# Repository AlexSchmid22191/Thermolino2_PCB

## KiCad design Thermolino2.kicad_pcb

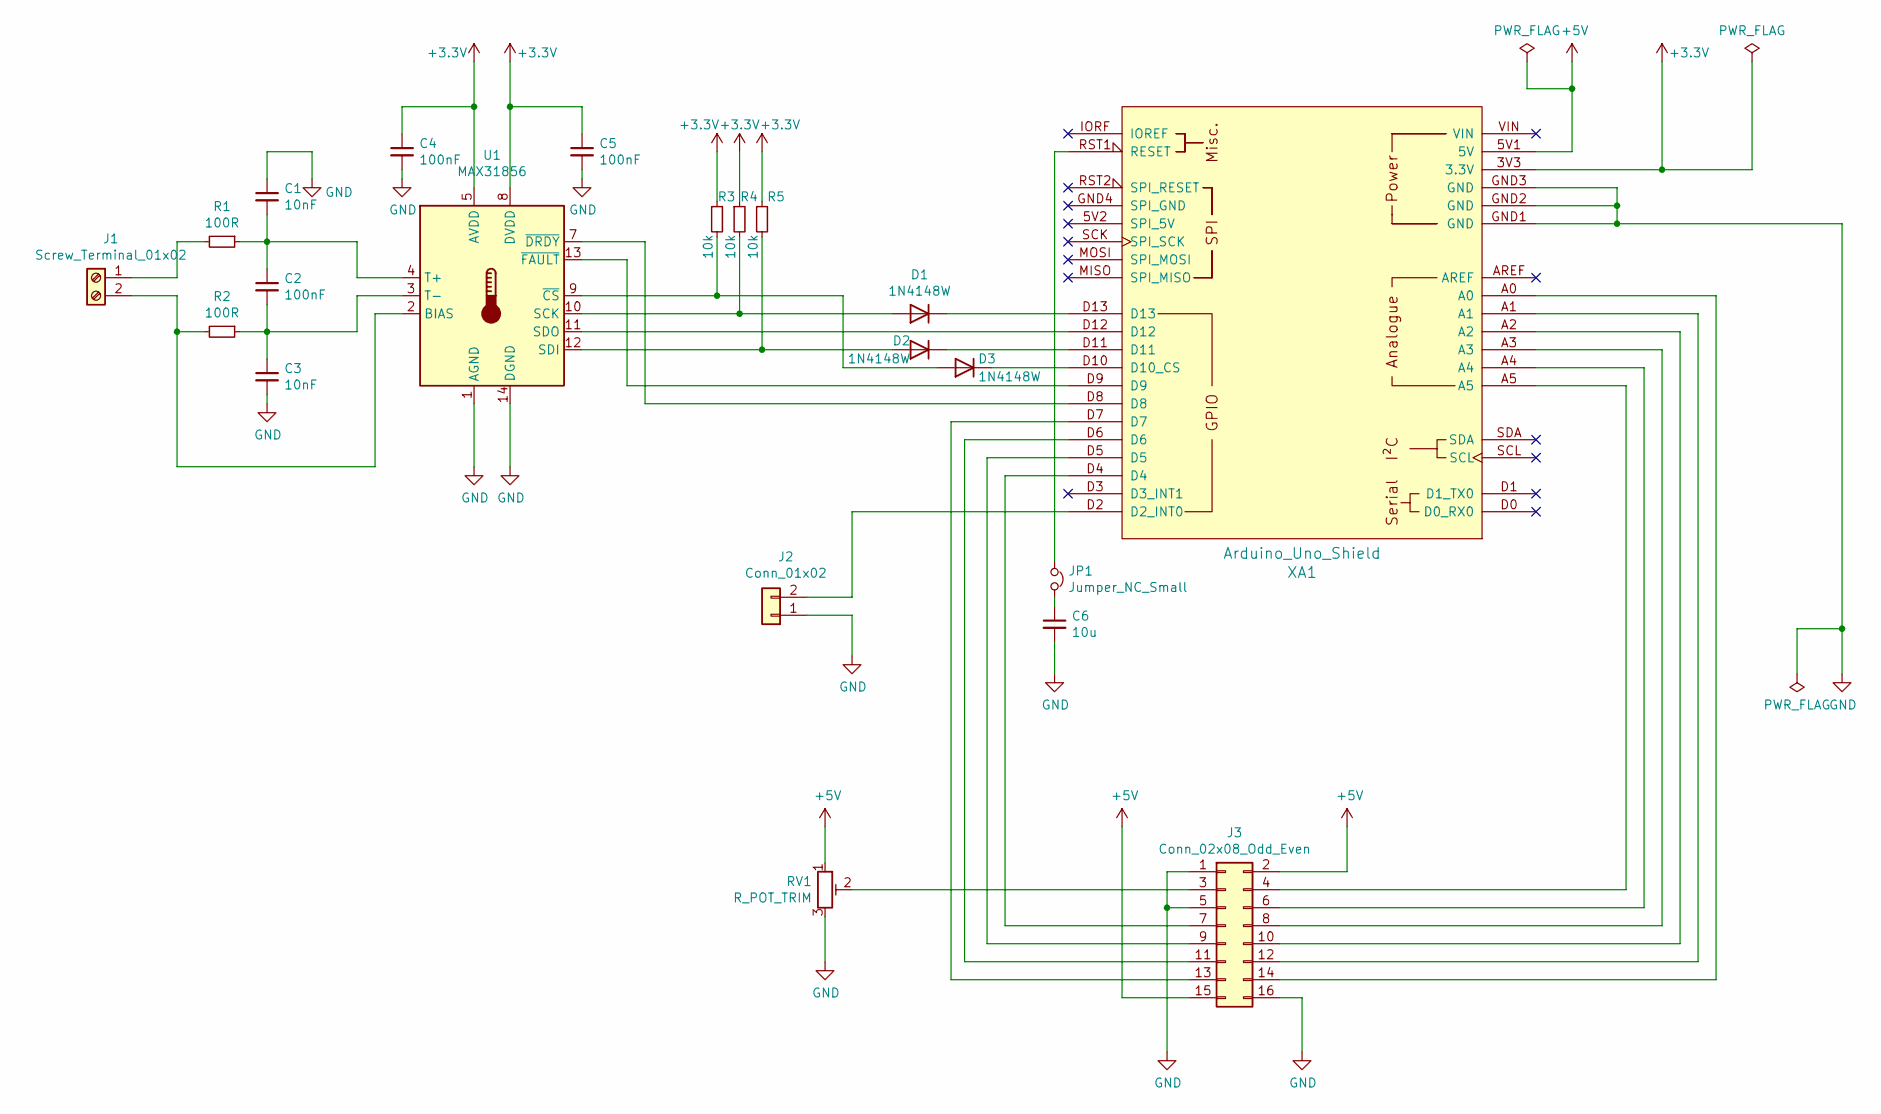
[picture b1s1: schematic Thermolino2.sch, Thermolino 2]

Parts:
C1, C3: 10nF; C_0603_1608Metric; LCSC C57112
C2, C4, C5: 100nF; C_0603_1608Metric; LCSC C14663
C6: 10u; C_0603_1608Metric_Pad1.05x0.95mm_HandSolder; LCSC C19702
D1, D2, D3: 1N4148W; D_SOD-123; LCSC C81598
J1: Screw_Terminal_01x02; Wurth_ScrewTerminal_02
J2: Conn_01x02; PinHeader_1x02_P2.54mm_Vertical
J3: Conn_02x08_Odd_Even; IDC_02x08
JP1: Jumper_NC_Small; PinHeader_1x02_P2.54mm_Vertical
R1, R2: 100R; R_0603_1608Metric; LCSC C22775
R3, R4, R5: 10k; R_0603_1608Metric; LCSC C25804
RV1: R_POT_TRIM; Vishay_TS53_Trimpot
U1: MAX31856; TSSOP-14_4.4x5mm_P0.65mm; LCSC C116632
XA1: Arduino_Uno_Shield

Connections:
+3V3: C4.1, C5.1, R3.1, R4.1, R5.1, U1.5 (AVDD), U1.8 (DVDD), XA1.3V3 (3.3V)
+5V: J3.2, J3.15, RV1.1, XA1.5V1 (5V)
GND: C1.1, C3.2, C4.2, C5.2, C6.2, J2.1, J3.1, J3.5, J3.16, RV1.3, U1.1 (AGND), U1.14 (DGND), XA1.GND1 (GND), XA1.GND2 (GND), XA1.GND3 (GND)
unnamed: C1.2, C2.1, R1.1, U1.4 (T+)
unnamed: C2.2, C3.1, R2.1, U1.3 (T-)
unnamed: C6.1, JP1.2
unnamed: D1.1 (K), XA1.D13
unnamed: D1.2 (A), R4.2, U1.10 (SCK)
unnamed: D2.1 (K), XA1.D11
unnamed: D2.2 (A), R5.2, U1.12 (SDI)
unnamed: D3.1 (K), XA1.D10 (D10_CS)
unnamed: D3.2 (A), R3.2, U1.9 (~CS)
unnamed: J1.1, R1.2
unnamed: J1.2, R2.2, U1.2 (BIAS)
unnamed: J2.2, XA1.D2 (D2_INT0)
unnamed: J3.3, RV1.2
unnamed: J3.4, XA1.A5
unnamed: J3.6, XA1.A4
unnamed: J3.7, XA1.D4
unnamed: J3.8, XA1.A3
unnamed: J3.9, XA1.D5
unnamed: J3.10, XA1.A2
unnamed: J3.11, XA1.D6
unnamed: J3.12, XA1.A1
unnamed: J3.13, XA1.D7
unnamed: J3.14, XA1.A0
unnamed: JP1.1, XA1.RST1 (RESET)
unnamed: U1.7 (~DRDY), XA1.D8
unnamed: U1.11 (SDO), XA1.D12
unnamed: U1.13 (~FAULT), XA1.D9

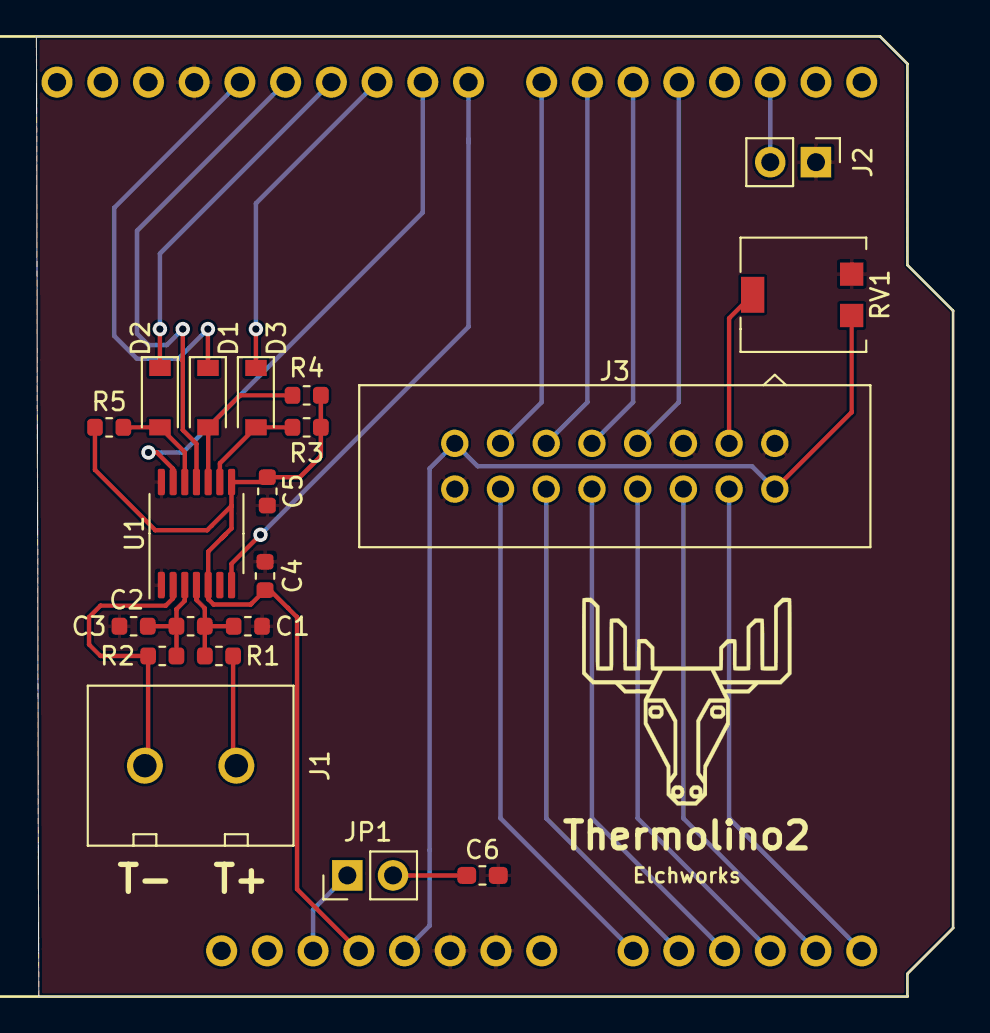
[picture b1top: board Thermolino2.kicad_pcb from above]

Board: 2 copper layers, 50.9 x 53.3 mm, 21 parts (0 on the bottom side), 30 nets.

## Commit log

2021-01-19 Initial
2021-02-02 Added Logo
